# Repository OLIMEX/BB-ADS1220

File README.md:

# BB-ADS1220
OSHW Open Source Hardware breakboard for ADS1220 Low Power Preciese 24-bit ADC from Texas Instruments

## Licensee
* Hardware is released under CERN Open Hardware Licence Version 2 -
Strongly Reciprocal
* Software is released under GPL3 Licensee
* Documentation is released under CC BY-SA 3.0

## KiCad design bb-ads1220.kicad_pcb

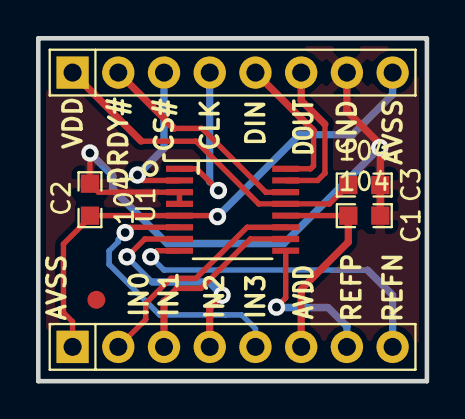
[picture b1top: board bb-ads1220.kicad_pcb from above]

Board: 2 copper layers, 21.6 x 19.0 mm, 5 parts (1 on the bottom side), 4 nets.

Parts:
C1, C2, C3: 104; C_0603
OLIMEX_LOGO**: OLIMEX_LOGO_TB
U1: ADS1220; TSSOP-16_4.4x5mm_Pitch0.65mm

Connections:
/AVSS: C2.1, U1.5
GND: C1.1, C2.2, C3.1, U1.3, U1.4
unnamed: C1.2, U1.12
unnamed: C3.2, U1.13

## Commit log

2015-06-26 initial release KiCAD files
2015-06-29 schematic update
2015-07-01 Added OLinuXino python example
2015-07-01 Deleted duplicated files
2020-04-29 update docs, software
2020-04-29 readme update
2020-04-29 pdf update

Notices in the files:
bb-ads1220.kicad_pcb:
(c) 2015
